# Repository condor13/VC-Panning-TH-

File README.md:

# VC-Panning-TH-
Voltage Controled Pan (Thru Hole) Eurorack
LM13700 Bassed vc-pan.

BOM

------##MISC##

100K potentionmeter                  (1) 

PJ302M Jacks                         (3) 

10k ohm                              (2) 

Transistor 2n3906                    (2) 

1N5819 Schottky Diodes               (2)

1N4148 Schottky Diodes               (2)

8 pin ic socket                      (1) 

14 pin ic socket                     (1)

16 pin ic socket                     (1) 

10 pin header                        (1) 

------##IC## 

LM13700N Operational Amplifier IC    (1) 

TL074 Quad Operational Amplifier     (1) 

TL072 LOW NOISE J-FET DUAL OP-AMP    (1) 

------##RESISTORS##

10k  OHM 1/4W 1% Metal Film Resistor (2)

100k OHM 1/4W 1% Metal Film Resistor (8)

150k OHM 1/4W 1% Metal Film Resistor (4)

220K OHM 1/4W 1% Metal Film Resistor (4)

560K OHM 1/4W 1% Metal Film Resistor (2) 

------##CAPS##

100n 0.1uF 50V                       (8)

10 uf electrolytic caps              (2)

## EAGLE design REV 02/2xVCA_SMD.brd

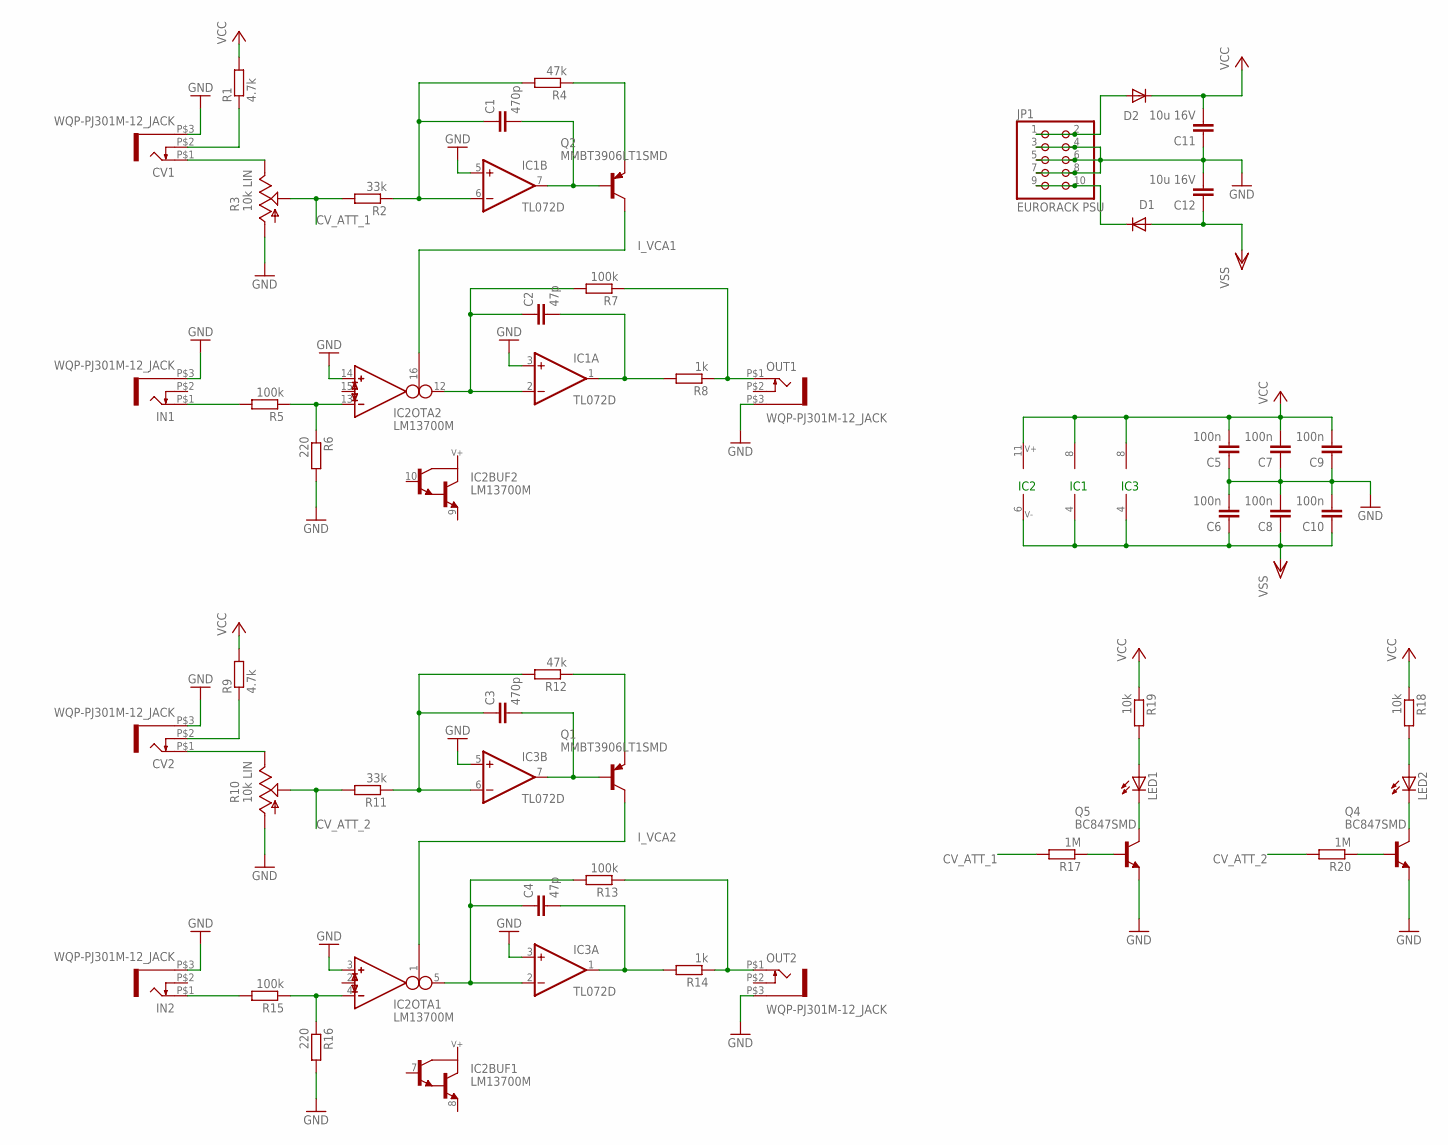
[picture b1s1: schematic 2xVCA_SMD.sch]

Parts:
C1, C3: 470p; C0603K
C2, C4: 47p; C0603K
C5, C6, C7, C8, C9, C10: 100n; C0603K
C11, C12: 10u 16V; C1206K
CV1, CV2: WQP-PJ301M-12_JACK
D1, D2: 1N5819HW; SOD123
IC1, IC3: TL072D; SO08
IC2: LM13700M; SO16
IN1, IN2: WQP-PJ301M-12_JACK
JP1: EURORACK PSU; 2X05
LED1, LED2: LED3MM
OUT1, OUT2: WQP-PJ301M-12_JACK
Q1, Q2: MMBT3906LT1SMD; SOT23-BEC
Q4, Q5: BC847SMD; SOT23
R1, R9: 4.7k; R0603
R2, R11: 33k; R0603
R3, R10: 10k LIN; ALPS_POT_VERTICAL
R4, R12: 47k; R0603
R5, R7, R13, R15: 100k; R0603
R6, R16: 220; R0603
R8, R14: 1k; R0603
R17, R20: 1M; R0603
R18, R19: 10k; R0603

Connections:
CV_ATT_1: R2.2, R3.P$2 (S), R17.2
CV_ATT_2: R10.P$2 (S), R11.2, R20.2
GND: C5.1, C6.2, C7.1, C8.2, C9.1, C10.2, C11.1, C12.2, CV1.P$3 (1), CV2.P$3 (1), IC1.3 (+IN), IC1.5 (+IN), IC2.3 (IN_P), IC2.14 (IN_P), IC3.3 (+IN), IC3.5 (+IN), IN1.P$3 (1), IN2.P$3 (1), JP1.3, JP1.4, JP1.5, JP1.6, JP1.7, JP1.8, OUT1.P$3 (1), OUT2.P$3 (1), Q4.2 (E), Q5.2 (E), R3.P$3 (A), R6.2, R10.P$3 (A), R16.2
I_VCA1: IC2.16 (I_BIAS), Q2.C
I_VCA2: IC2.1 (I_BIAS), Q1.C
unnamed: IN2.P$1 (2), R15.2
unnamed: CV1.P$2 (3), R1.1
unnamed: CV1.P$1 (2), R3.P$1 (E)
unnamed: Q5.1 (B), R17.1
unnamed: C1.1, IC1.6 (-IN), R2.1, R4.2
unnamed: C2.1, IC1.2 (-IN), IC2.12 (OUT), R7.2
unnamed: C1.2, IC1.7 (OUT), Q2.B
unnamed: Q2.E, R4.1
unnamed: IC2.13 (IN_N), R5.1, R6.1
unnamed: IC2.4 (IN_N), R15.1, R16.1
unnamed: IN1.P$1 (2), R5.2
unnamed: C2.2, IC1.1 (OUT), R8.2
unnamed: OUT1.P$1 (2), R7.1, R8.1
unnamed: C4.1, IC2.5 (OUT), IC3.2 (-IN), R13.2
unnamed: CV2.P$2 (3), R9.1
unnamed: CV2.P$1 (2), R10.P$1 (E)
unnamed: LED1.A, R19.2
unnamed: C3.1, IC3.6 (-IN), R11.1, R12.2
unnamed: OUT2.P$1 (2), R13.1, R14.1
unnamed: C3.2, IC3.7 (OUT), Q1.B
unnamed: Q1.E, R12.1
unnamed: C4.2, IC3.1 (OUT), R14.2
unnamed: LED1.K (C), Q5.3 (C)
unnamed: LED2.A, R18.2
unnamed: LED2.K (C), Q4.3 (C)
unnamed: Q4.1 (B), R20.1
unnamed: D2.A, JP1.1, JP1.2
unnamed: D1.C, JP1.9, JP1.10
VCC: C5.2, C7.2, C9.2, C11.2, D2.C, IC1.8 (V+), IC2.11 (V+), IC3.8 (V+), R1.2, R9.2, R18.1, R19.1
VSS: C6.1, C8.1, C10.1, C12.1, D1.A, IC1.4 (V-), IC2.6 (V-), IC3.4 (V-)

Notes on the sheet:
IC1
IC2
IC3

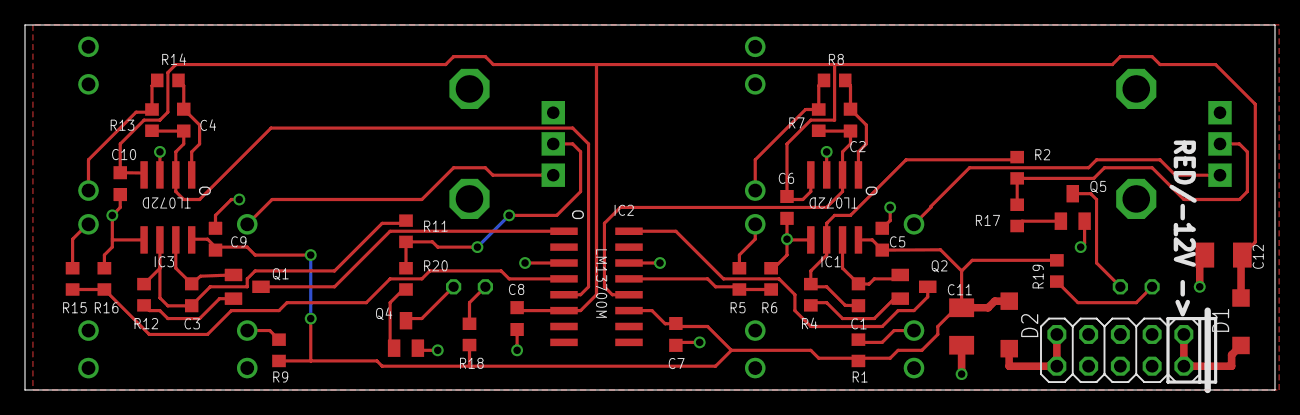
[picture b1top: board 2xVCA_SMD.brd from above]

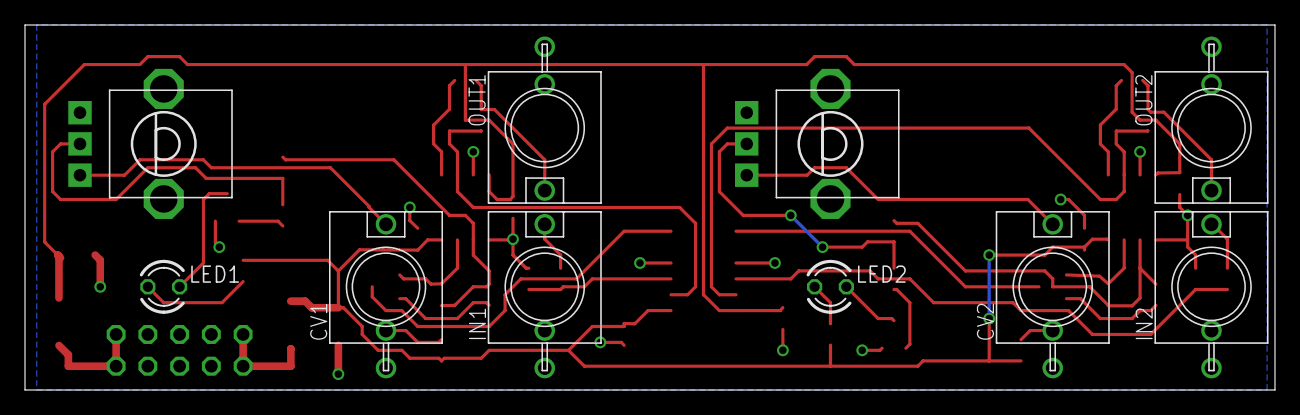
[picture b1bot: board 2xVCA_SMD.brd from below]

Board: 2 copper layers, 100.0 x 29.2 mm, 50 parts (10 on the bottom side), 35 nets.

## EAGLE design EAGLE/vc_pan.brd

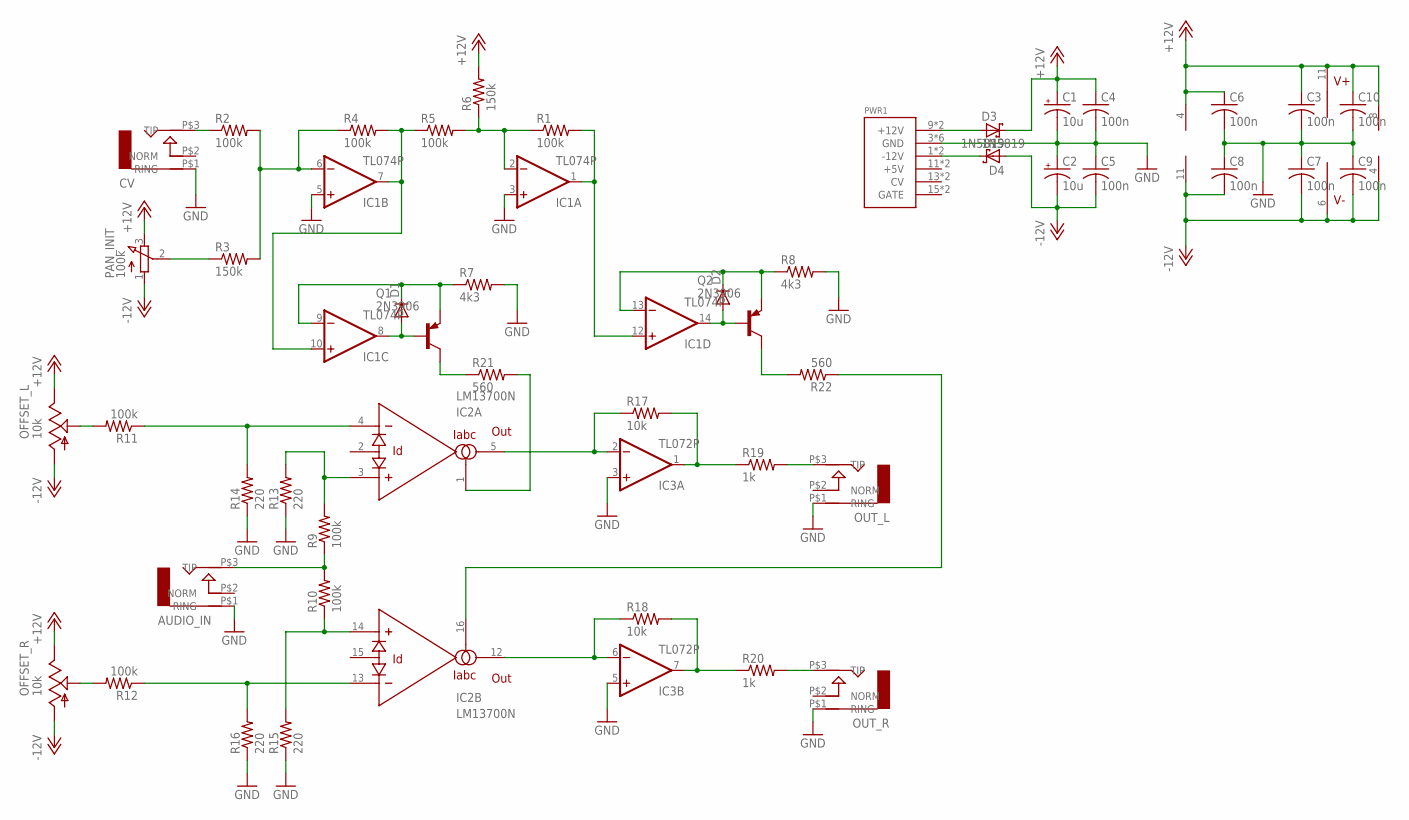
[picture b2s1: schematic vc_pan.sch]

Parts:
AUDIO_IN: AUDIO-JACK; ERTHENVAR-JACK-90DEG
C1, C2: 10u; B45181A
C3, C4, C5, C6, C7, C8, C9, C10: 100n; C050-024X044
CV: AUDIO-JACK; ERTHENVAR-JACK-90DEG
D1, D2: 1N4148DO35-7; DO35-7
D3, D4: 1N5819; DO41-7.6
IC1: TL074P; DIL14
IC2: LM13700N; DIL16
IC3: TL072P; DIL08
OFFSET_L: 10k; B64Y
OFFSET_R: 10k; B64Y
OUT_L: AUDIO-JACK; ERTHENVAR-JACK-90DEG
OUT_R: AUDIO-JACK; ERTHENVAR-JACK-90DEG
PAN_INIT: 100k; 3RP/1610N
PWR1: POWER; POWER_16
Q1, Q2: 2N3906; TO92
R1, R2, R4, R5, R9, R10, R11, R12: 100k; 0207/10
R3, R6: 150k; 0207/10
R7, R8: 4k3; 0207/10
R13, R14, R15, R16: 220; 0207/10
R17, R18: 10k; 0207/10
R19, R20: 1k; 0207/10
R21, R22: 560; 0207/10

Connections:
+12V: C1.+, C3.1, C4.1, C6.1, C10.1, D3.C, IC1.4 (V+), IC2.11 (V+), IC3.8 (V+), OFFSET_L.E, OFFSET_R.E, PAN_INIT.3 (E), R6.2
-12V: C2.-, C5.2, C7.2, C8.2, C9.2, D4.A, IC1.11 (V-), IC2.6 (V-), IC3.4 (V-), OFFSET_L.A, OFFSET_R.A, PAN_INIT.1 (A)
GND: AUDIO_IN.P$1 (RING), C1.-, C2.+, C3.2, C4.2, C5.1, C6.2, C7.1, C8.1, C9.1, C10.2, CV.P$1 (RING), IC1.3 (+IN), IC1.5 (+IN), IC3.3 (+IN), IC3.5 (+IN), OUT_L.P$1 (RING), OUT_R.P$1 (RING), PWR1.3 (GND), PWR1.4 (GND), PWR1.5 (GND), PWR1.6 (GND), PWR1.7 (GND), PWR1.8 (GND), R7.2, R8.2, R13.1, R14.1, R15.1, R16.1
unnamed: D3.A, PWR1.9 (+12V), PWR1.10 (+12V)
unnamed: D4.C, PWR1.1 (-12V), PWR1.2 (-12V)
unnamed: CV.P$3 (TIP), R2.1
unnamed: PAN_INIT.2 (S), R3.1
unnamed: IC1.6 (-IN), R2.2, R3.2, R4.1
unnamed: IC1.7 (OUT), IC1.10 (+IN), R4.2, R5.1
unnamed: IC1.2 (-IN), R1.1, R5.2, R6.1
unnamed: IC1.1 (OUT), IC1.12 (+IN), R1.2
unnamed: D1.A, IC1.8 (OUT), Q1.2 (B)
unnamed: D2.A, IC1.14 (OUT), Q2.2 (B)
unnamed: D1.C, IC1.9 (-IN), Q1.3 (E), R7.1
unnamed: D2.C, IC1.13 (-IN), Q2.3 (E), R8.1
unnamed: AUDIO_IN.P$3 (TIP), R9.1, R10.2
unnamed: IC2.3 (+IN), R9.2, R13.2
unnamed: IC2.14 (+IN), R10.1, R15.2
unnamed: IC2.4 (-IN), R11.1, R14.2
unnamed: IC2.13 (-IN), R12.1, R16.2
unnamed: OFFSET_R.S, R12.2
unnamed: OFFSET_L.S, R11.2
unnamed: IC3.7 (OUT), R18.2, R20.1
unnamed: IC2.5 (OUT), IC3.2 (-IN), R17.1
unnamed: IC2.12 (OUT), IC3.6 (-IN), R18.1
unnamed: IC3.1 (OUT), R17.2, R19.1
unnamed: OUT_L.P$3 (TIP), R19.2
unnamed: OUT_R.P$3 (TIP), R20.2
unnamed: Q2.1 (C), R22.2
unnamed: IC2.16 (IABC), R22.1
unnamed: IC2.1 (IABC), R21.2
unnamed: Q1.1 (C), R21.1

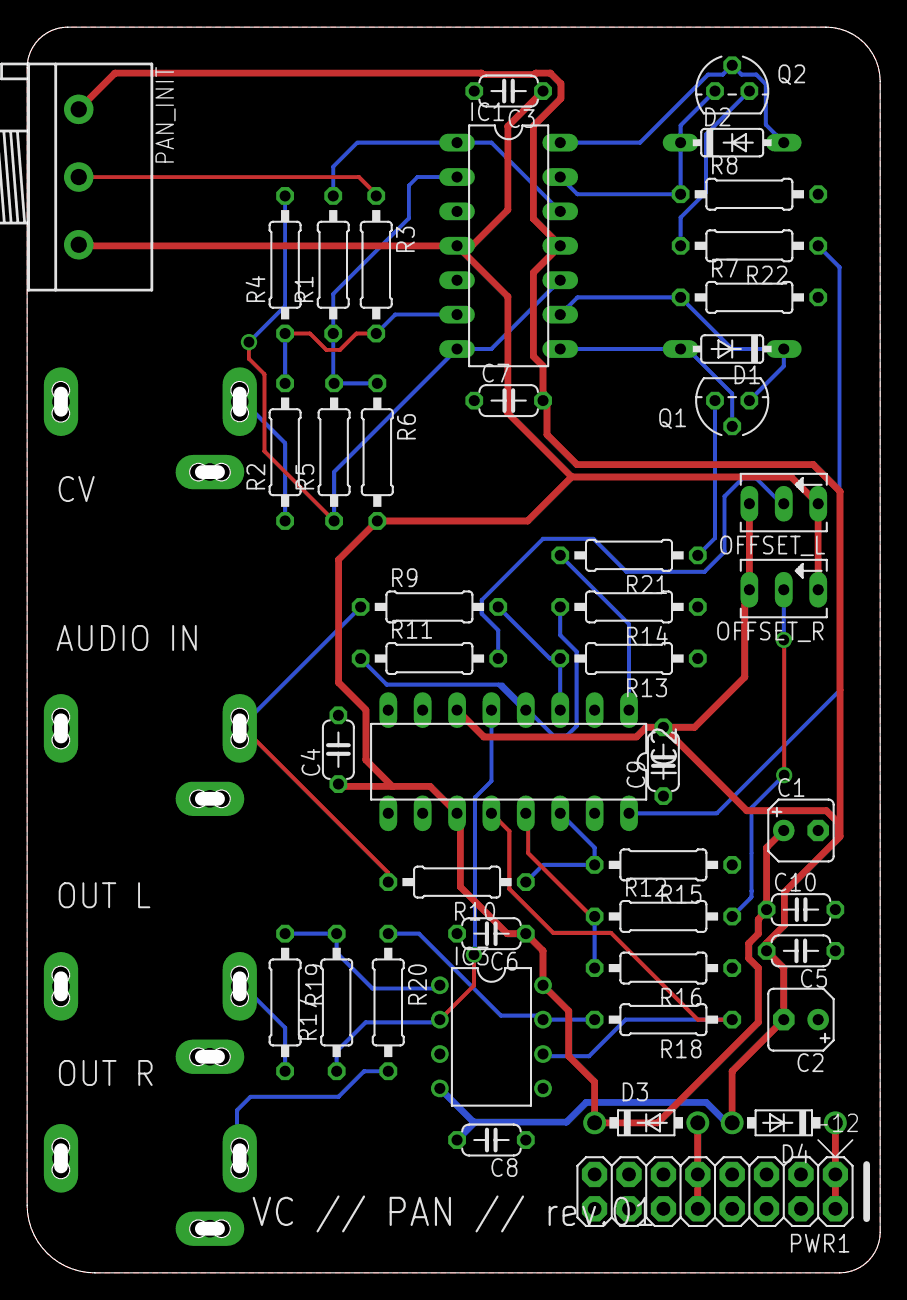
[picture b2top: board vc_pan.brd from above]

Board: 2 copper layers, 63.0 x 92.0 mm, 49 parts (0 on the bottom side), 32 nets.

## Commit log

2018-01-17 REV - 02
